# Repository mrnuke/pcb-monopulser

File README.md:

# Monopulser

An adjustable width single-shot pulse generator.

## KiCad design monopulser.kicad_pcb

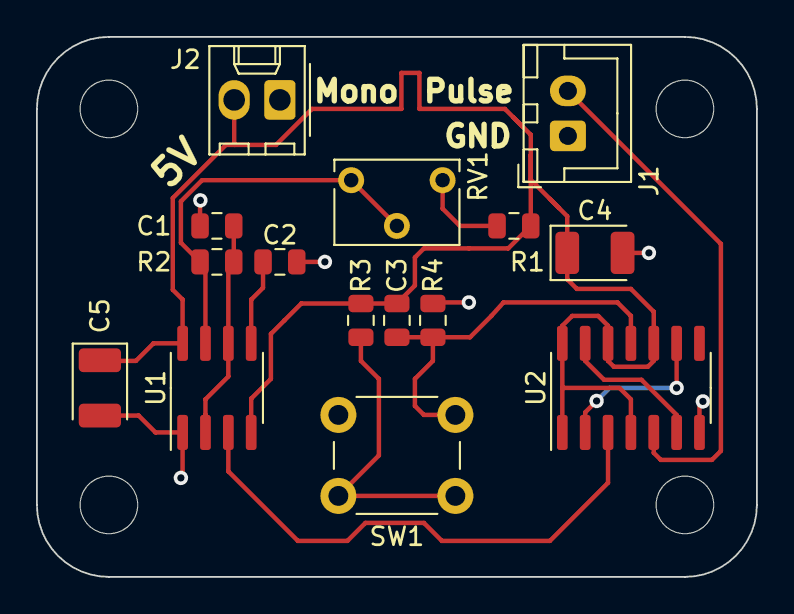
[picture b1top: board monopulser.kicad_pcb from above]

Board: 2 copper layers, 40.0 x 30.0 mm, 15 parts (0 on the bottom side), 12 nets.

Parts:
C1, C2, C3: 47n; C_0805_2012Metric
C4, C5: 4.7u; CP_EIA-3528-21_Kemet-B
J1: Conn_01x02_Male; JST_XH_B2B-XH-A_1x02_P2.50mm_Vertical
J2: Conn_01x02_Male; Molex_KK-254_AE-6410-02A_1x02_P2.54mm_Vertical
R1, R3, R4: 1k; R_0805_2012Metric
R2: 6.7k; R_0805_2012Metric
RV1: 100k; Potentiometer_Bourns_3266W_Vertical
SW1: MM; SW_PUSH_6mm
U1: LM555; SOIC-8_3.9x4.9mm_P1.27mm
U2: 74HC74; SOIC-14_3.9x8.7mm_P1.27mm

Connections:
/CLK: U1.3, U2.3
/PULSE: J1.2, U2.5
GND: C1.2, C2.2, C4.2, C5.2, J1.1, J2.1, R4.2, U1.1, U2.7
unnamed: C1.1, R2.1, U1.2, U1.6
unnamed: C2.1, U1.5
unnamed: C3.2, R4.1, SW1.2, U2.11
unnamed: R1.1, RV1.1
unnamed: R2.2, RV1.2, RV1.3, U1.7
unnamed: R3.1, SW1.1
unnamed: U2.2, U2.9
unnamed: U2.6, U2.13
VCC: C3.1, C4.1, C5.1, J2.2, R1.2, R3.2, U1.4, U1.8, U2.1, U2.4, U2.10, U2.12, U2.14

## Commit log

2020-04-02 Import schematic and board layout
